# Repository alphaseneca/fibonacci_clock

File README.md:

<!-- # fibonacci_clock

A unique clock that uses the Fibonacci sequence to display time with colored squares, combining math and art in an innovative timekeeping design.

## Working

It works by lighing up a segment of the matrix based on the time in the Fibonacci sequence. If the time is 6:42 it will light up the segment **1** and **5** to **RED** which will add to give the hour 6. And for minutes it will light up the segment **3** and **5** to **BLUE** which will add to **8*5** equals to **40** minutes. And since the segment **5** are lit by both the hour and minutes it will change the colour to **GREEN** to show the overlap in the both hour and minutes.

> The segment can only represent between **1 - 12** and to represent the minutes we are multiplying it by 5.
> Since the increments are in every 5 minutes thus the time can be between **40 - 45** Minutes.

Working Image:

 -->

# Fibonacci Clock

A unique clock project that combines **math and electronics** using the Fibonacci sequence to display time with colored segments. Powered by a **Wemos D1 Mini**, it fetches the current time using **NTP**. This repository serves as a **learning journal**, tracking the development process, inspirations, troubleshooting, and future improvements.

---

---

## Repository Structure

- **`images/`**: Photos of the clock and its working principle.
- **`fibonacci_clock_code/`**: Contains the code to run the Fibonacci clock logic.
<!-- - **`References/`**: Resources and ideas that inspired the project.   -->
- **`fibonacci_clock_pcb/`**: Files and documentation for the PCB design.
- **`debugging/`**: Logs of issues encountered and solutions applied during development.
<!-- - **`Inspiration.md`**: Notes on inspirations and design choices, with references for future enhancements. -->

---

## How It Works

The Fibonacci Clock displays time by lighting up segments of a matrix corresponding to Fibonacci numbers.

- **Microcontroller**: Wemos D1 Mini (ESP8266).
- **Time Sync**: Fetches the current time via **NTP** (Network Time Protocol).
- **Hour Representation**:  
  Example: If the time is **6:42**, segments **1** and **5** are lit **RED**, which sum to **6** for the hour.
- **Minute Representation**:  
  For **42 minutes**, segments **3** and **5** are lit **BLUE**, resulting in **(3 + 5) × 5 = 40 minutes**.
- **Overlap**:  
  When a segment represents both hours and minutes (e.g., segment **5**), it is lit **GREEN** to indicate overlap.

**Working Principle Diagram**:  

> Segments only represent numbers between **1 - 12**, and minute values are scaled by **multiplying by 5**.  
> Time increments are in 5-minute intervals, so valid minute values range between **40 - 45 minutes**.

---

## The Journey So Far

Building this clock has been an exciting adventure. It started as a simple idea to make a desktop artpiece that is bit unique and looks cool and ended up being a timekeeping device. Using the **Wemos D1 Mini** to sync time with NTP added complexity but opened new possibilities.

 <!-- Handling **network connectivity** and **color overlaps** provided valuable learning experiences. -->

Creating the PCB design was also a journey in its own. I started with the prefboard and the main project is still on the prefboard but for the further development and to make the device look clean and more presentable the [PCB design](fibonacci_clock_pcb/fibonacci_clock_pcb.jpg) was created.

The pcb that I created is not complete. It is still a work in progress and nowhere near to the original design. I am planning to make the project like the main original design itself.

Future iterations may include **offline timekeeping** by integrating an **RTC module** to eliminate reliance on NTP. Wireless control and animations are also on the horizon!

---

## Debugging Log

- **Issue 1**: Incorrect color when hours and minutes overlapped.
  - **Solution**: Modified the RGB blending logic to correctly show GREEN for overlaps.
- **Issue 2**: Incorrect minute calculation when sum exceeded valid range.
  - **Solution**: Added checks to restrict values between 0-12 for valid Fibonacci sums.
- **Issue 3**: The light is not bright enough and flickers a lot.
  - **Solution**: Removed the delay in the main loop to reduce flickering.
    > Just a current solution though. Planning to remove the second solution in the future busing **MAX7219** chip rather than the **LM74HC595** chip.

---

## Future Improvements

- **RTC Integration**: Add an **RTC module** (like DS3231) for offline timekeeping.
- **PCB Enhancements**: Optimize the layout for smaller size and better wiring.
- **Dynamic Patterns**: Add animations or interactive light sequences. There could be much more animations and the rgb led can be used to show some patterns.
- **Battery Power**: Implement battery-powered functionality for portability.

---

## References and Inspirations

- Original inspiration from the [Kickstarter Campaign](https://www.kickstarter.com/projects/basbrun/fibonacci-clock-an-open-source-clock-for-nerds-wit).
- Building process from [Instructables project](https://www.instructables.com/The-Fibonacci-Clock/).
- Video from [Steve Ramsey on Youtube](https://www.youtube.com/watch?v=YIN95L4BdLk) building the clock .

<!-- [The guardian](https://www.theguardian.com/science/alexs-adventures-in-numberland/2015/may/09/fibonacci-clock-can-you-tell-the-time-on-the-worlds-most-stylish-nerd-timepiece) also covered the design of the fibonacci clock. -->

<!-- - Visual design inspired by [Fibonacci Artworks](https://example.com). -->

---

This repository will continue to evolve as I experiment with new features and improvements.

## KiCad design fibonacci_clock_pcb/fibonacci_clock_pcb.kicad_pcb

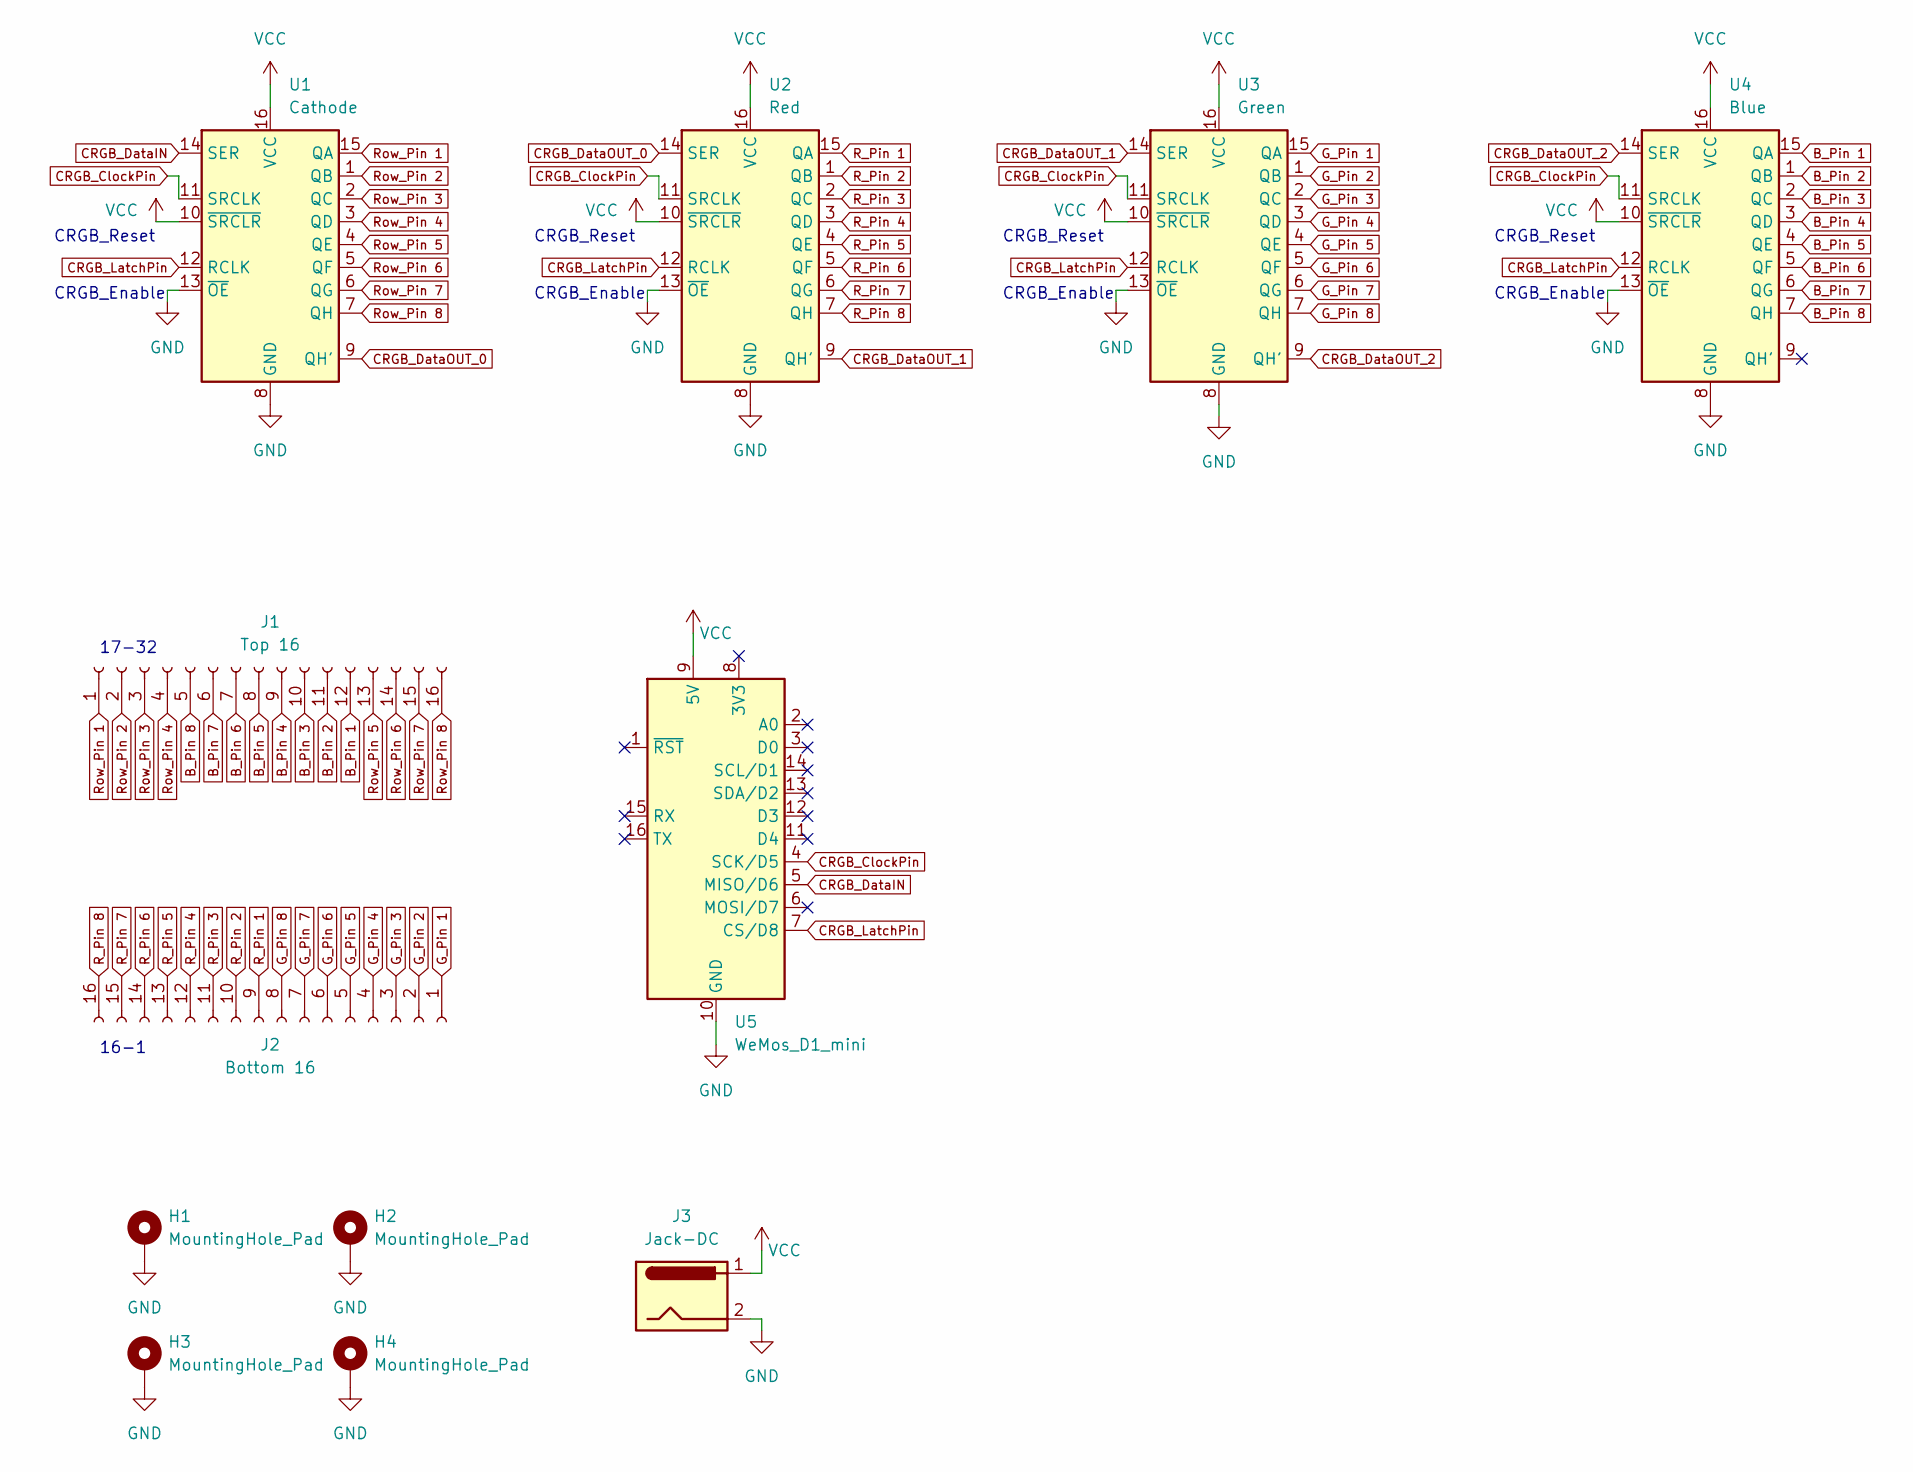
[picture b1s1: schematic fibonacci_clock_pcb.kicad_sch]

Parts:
H1, H2, H3, H4: MountingHole_Pad; MountingHole_3mm_Pad_TopBottom
J1: Top 16; PinSocket_1x16_P2.54mm_Vertical
J2: Bottom 16; PinSocket_1x16_P2.54mm_Vertical
J3: Jack-DC; BarrelJack_Horizontal
U1: Cathode; DIP-16_W7.62mm
U2: Red; DIP-16_W7.62mm
U3: Green; DIP-16_W7.62mm
U4: Blue; DIP-16_W7.62mm
U5: WeMos_D1_mini; WEMOS_D1_mini_light

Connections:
B_Pin 1: J1.12, U4.15 (QA)
B_Pin 2: J1.11, U4.1 (QB)
B_Pin 3: J1.10, U4.2 (QC)
B_Pin 4: J1.9, U4.3 (QD)
B_Pin 5: J1.8, U4.4 (QE)
B_Pin 6: J1.7, U4.5 (QF)
B_Pin 7: J1.6, U4.6 (QG)
B_Pin 8: J1.5, U4.7 (QH)
CRGB_ClockPin: U1.11 (SRCLK), U2.11 (SRCLK), U3.11 (SRCLK), U4.11 (SRCLK), U5.4 (SCK/D5)
CRGB_DataIN: U1.14 (SER), U5.5 (MISO/D6)
CRGB_DataOUT_0: U1.9 (QH'), U2.14 (SER)
CRGB_DataOUT_1: U2.9 (QH'), U3.14 (SER)
CRGB_DataOUT_2: U3.9 (QH'), U4.14 (SER)
CRGB_LatchPin: U1.12 (RCLK), U2.12 (RCLK), U3.12 (RCLK), U4.12 (RCLK), U5.7 (CS/D8)
GND: H1.1, H2.1, H3.1, H4.1, J3.2, U1.8 (GND), U1.13 (~OE), U2.8 (GND), U2.13 (~OE), U3.8 (GND), U3.13 (~OE), U4.8 (GND), U4.13 (~OE), U5.10 (GND)
G_Pin 1: J2.1, U3.15 (QA)
G_Pin 2: J2.2, U3.1 (QB)
G_Pin 3: J2.3, U3.2 (QC)
G_Pin 4: J2.4, U3.3 (QD)
G_Pin 5: J2.5, U3.4 (QE)
G_Pin 6: J2.6, U3.5 (QF)
G_Pin 7: J2.7, U3.6 (QG)
G_Pin 8: J2.8, U3.7 (QH)
R_Pin 1: J2.9, U2.15 (QA)
R_Pin 2: J2.10, U2.1 (QB)
R_Pin 3: J2.11, U2.2 (QC)
R_Pin 4: J2.12, U2.3 (QD)
R_Pin 5: J2.13, U2.4 (QE)
R_Pin 6: J2.14, U2.5 (QF)
R_Pin 7: J2.15, U2.6 (QG)
R_Pin 8: J2.16, U2.7 (QH)
Row_Pin 1: J1.1, U1.15 (QA)
Row_Pin 2: J1.2, U1.1 (QB)
Row_Pin 3: J1.3, U1.2 (QC)
Row_Pin 4: J1.4, U1.3 (QD)
Row_Pin 5: J1.13, U1.4 (QE)
Row_Pin 6: J1.14, U1.5 (QF)
Row_Pin 7: J1.15, U1.6 (QG)
Row_Pin 8: J1.16, U1.7 (QH)
VCC: J3.1, U1.10 (~SRCLR), U1.16 (VCC), U2.10 (~SRCLR), U2.16 (VCC), U3.10 (~SRCLR), U3.16 (VCC), U4.10 (~SRCLR), U4.16 (VCC), U5.9 (5V)

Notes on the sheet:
CRGB_Enable
CRGB_Reset
17-32
16-1

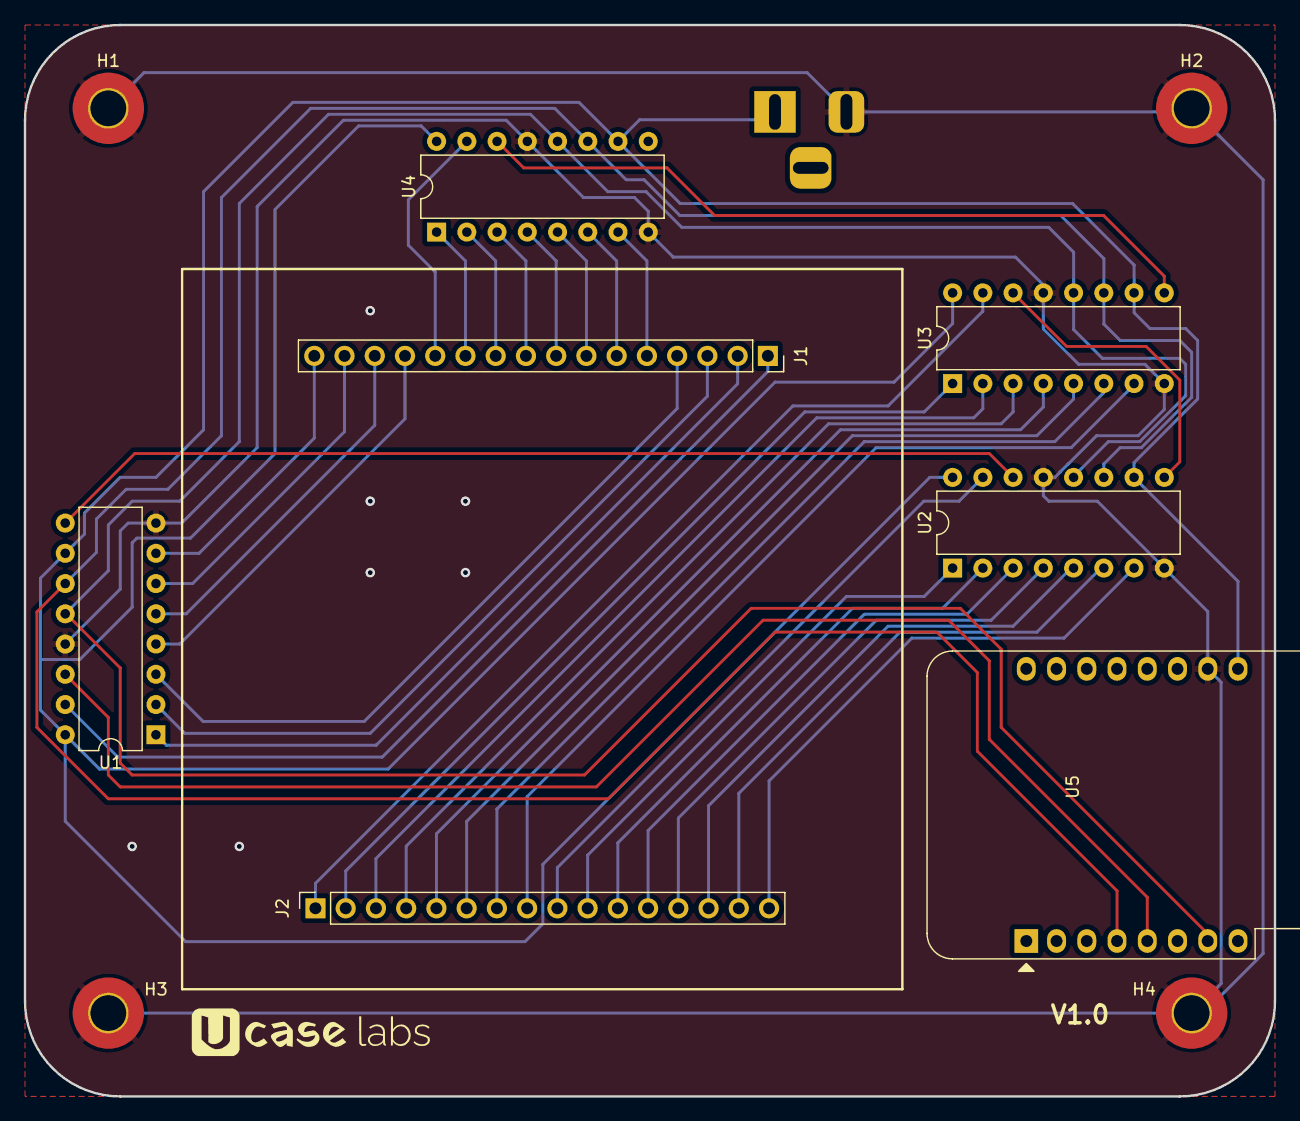
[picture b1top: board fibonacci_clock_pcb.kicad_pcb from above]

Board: 2 copper layers, 105.0 x 90.0 mm, 12 parts (1 on the bottom side), 40 nets.

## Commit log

2024-07-15 added gitignore file
2024-07-15 added images and updated the README
2024-07-17 added wifimanager and uploaded all the remaining files.
2024-10-25 Added the new images and the production images
2024-10-25 Revamped the readme
2024-10-25 resized the images
